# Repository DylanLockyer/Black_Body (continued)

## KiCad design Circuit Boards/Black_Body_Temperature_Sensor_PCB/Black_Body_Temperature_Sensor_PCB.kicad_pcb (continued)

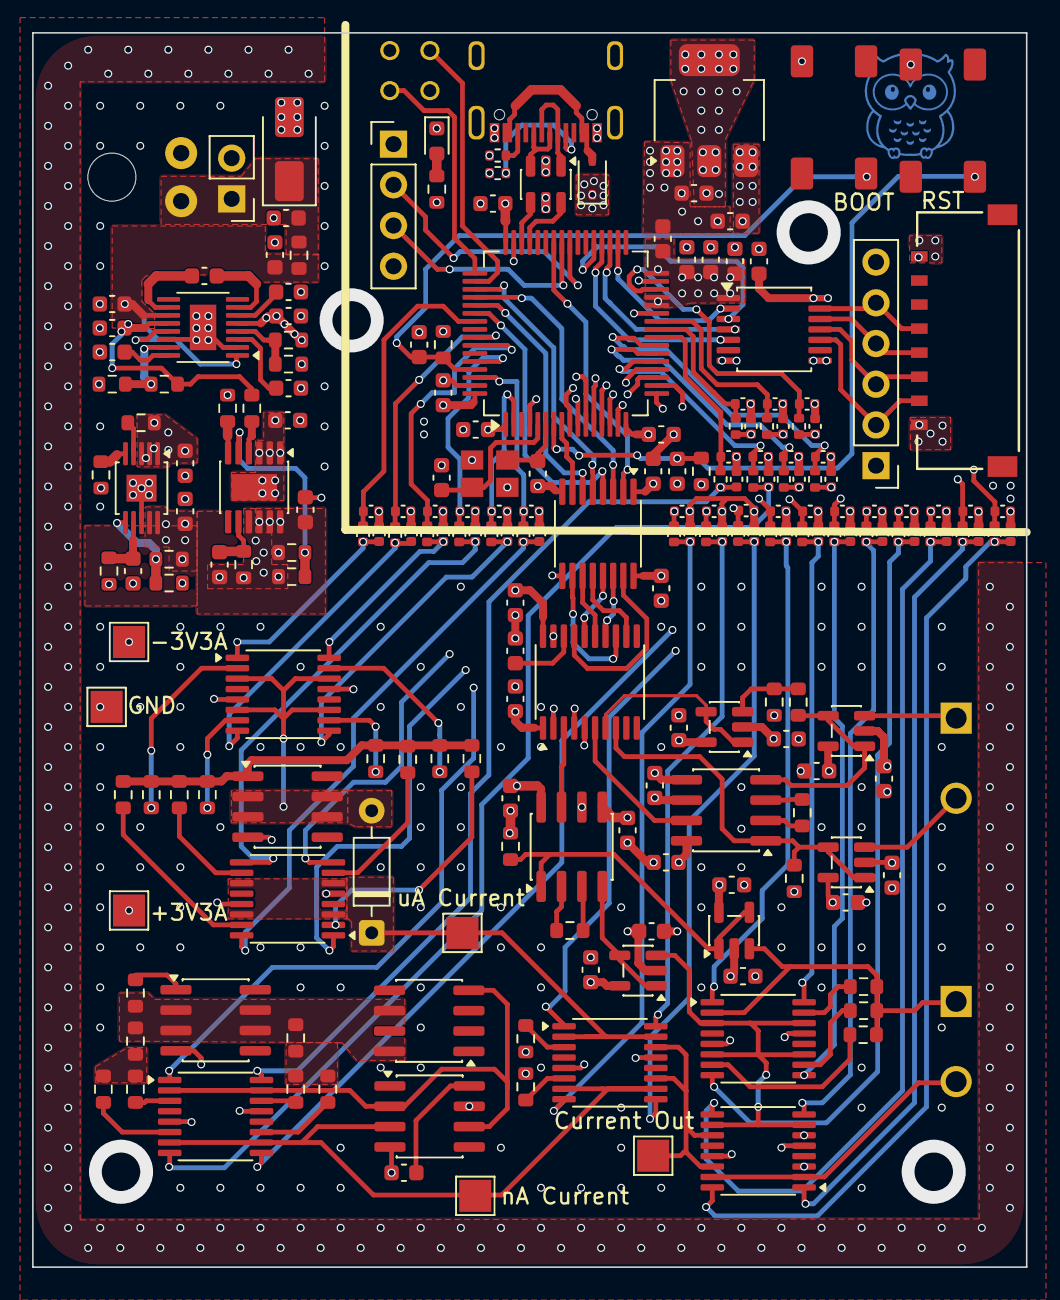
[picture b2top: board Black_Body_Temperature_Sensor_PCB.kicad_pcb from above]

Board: 6 copper layers, 62.0 x 77.0 mm, 216 parts (0 on the bottom side), 155 nets.

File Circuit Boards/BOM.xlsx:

Designator | Footprint | Quantity | Value | LCSC Part #
C201, C202, C203, C204, C205, C206, C207, C208, C209, C210, C211, C212, C213, C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 | 0402 | 48 | 2u2 | GRM155R61E225ME15D
C309 | 0603 | 1 | 200pf | CL10C201JB8NNNC
C501 | 0603 | 1 | 220nf | GCM188R71H224KA64D
C502, C503, C504, C505, C506, C507, C508, C509, C510, C511, C512, C513, C514, C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 | 0603 | 29 | 0.1uf | CL10B104KB8NNNC
C601, C602, C606, C607, C609, C614, C615, C712 | 0603 | 8 | 10uf | GRM188R6YA106MA73D
C603 | 0603 | 1 | 1uf | C0603C105K4RACTU
C604, C605 | 0603 | 2 | 10nf | CL10B103KB8NNNC
C608, C610, C611, C612, C613 | 0603 | 5 | 4.7uf | CL10A475KO8NNNC
C703, C705 | 0603 | 2 | 28pf | CL10C270JB8NNNC
C715 | 0603 | 1 | 22uf | CL10A226MP8NUNE
D201 | D_DO-35_SOD27_P7.62mm_Horizontal | 1 | 1N457 | 1N457
D301 | SOIC-8_3.9x4.9mm_P1.27mm | 1 | LT1004-1.2 | LT1004CS8-1.2#TRPBF
D601 | D_SMA | 1 | SMAJ24A | SMAJ24A
D701 | D_SOD-323 | 1 | 1N5819WS | 1N5819WS
J401, J402 | CUI_TB002-500-02BE | 2 | Screw_Terminal_01x02 | TB002-500-02BE
J702 | CONN_5040500891_MOL | 1 | 5040500891 | 5040500891
J703 | UJ20-C-H-G-SMT-1-P16-TR | 1 | USB_C_Receptacle_USB2.0_16P | UJ20-C-H-G-SMT-1-P16-TR
P601 | 436500200 2-pin | 1 | 436500200 | 436500200
Q201, Q202, Q301, Q401, Q402, Q403 | TSSOP-16_4.4x5mm_P0.65mm | 6 | TMUX1112PWR | TMUX1112PWR
R201, R202, R203, R204, R205, R206, R207, R208, R301, R302, R303, R304, R401, R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 | 0402 | 26 | 5.1k | RT0402BRD075K1L
R209 | 0603 | 1 | 133 | RQ73C1J133RBTD
R210, R211 | 0603 | 2 | 1.33k | ERA-3AEB1331V
R212, R213 | 0603 | 2 | 13.3k | ERA-3AEB1332V
R214, R215 | 0603 | 2 | 134k | ERA-3AEB1333V
R216 | 0603 | 1 | 1.33M | RK73H1JTTD1334F
R305, R502, R504 | 0603 | 3 | 10M | CRCW060310M0DHEAP
R306 | 0603 | 1 | 22.6k | ERA-3AEB2262V
R307 | 0603 | 1 | 100k | ERA-3AEB104V
R308 | 0603 | 1 | 100M | HVC0603T1006FET
R309 | 0603 | 1 | 226k | ERA-3AEB2263V
R310 | 0603 | 1 | 1M | RN73H1JTTD1004B25
R311 | 0603 | 1 | 2.7k | ERA-3AEB272V
R405 | 0603 | 1 | 4.99 | RN73C1J4R99BTD
R406, R606, R616 | 0603 | 3 | 500 | ERA-3AEB4990V
R407, R605, R608 | 0603 | 3 | 33.2k | ERA-3AEB3322V
R412, R413, R505, R506, R703, R704 | 0603 | 6 | 10k | ERA-3AEB103V
R501, R503 | 0603 | 2 | 50 | ERA-3AEB49R9V
R601, R604 | 0603 | 2 | 569k | RN73H1JTTD5693B50
R602, R603, R607, R609 | 0603 | 4 | 180k | ERA-3AEB184V
R610 | 0603 | 1 | 7.5k | ERA-3AEB752V
R611, R613 | 0603 | 2 | 448k | RT0603BRD07448KL
R612, R614 | 0603 | 2 | 50k | RT0603BRD0750KL
SW701, SW702 | 430471035826 | 2 | SW_MEC_5E | 430471035826
U201, U301 | SOIC-8_3.9x4.9mm_P1.27mm | 2 | LM334M | LM334M
U302 | SOIC-8_3.9x4.9mm_P1.27mm | 1 | LT1008 | LT1008S8#PBF
U501, U502, U503, U504, U509 | SOT-23-5 | 5 | OPA376xxDBV | OPA376AIDBVR
U505, U506 | SOIC-8_3.9x4.9mm_P1.27mm | 2 | AD8421ARZ | AD8421ARZ
U507 | TSSOP-20_4.4x6.5mm_P0.65mm | 1 | ADS131M04xPW | ADS131M04IPWR
U508 | SSOP-16_3.9x4.9mm_P0.635mm | 1 | ISO7762FDBQ | ISO7762FDBQ
U601 | MSOP-16-1EP_3x4.039mm_P0.5mm_EP1.651x2.845mm | 1 | LTC3260xMSE | LTC3260EMSE#TRPBF
U602 | MSOP-12-1EP_3x4.039mm_P0.65mm_EP1.651x2.845mm | 1 | LT3094xMSE | LT3094EMSE#TRPBF
U603 | MSOP-10-1EP_3x3mm_P0.5mm_EP1.68x1.88mm | 1 | LT3042xMSE | LT3042EMSE#TRPBF
U701 | TSSOP-14_4.4x5mm_P0.65mm | 1 | TXU0304 | TXU0304
U702 | ABM8G-25.000MHZ-18-D2Y-T | 1 | ABM8G-25.000MHZ-18-D2Y-T | ABM8G-25.000MHZ-18-D2Y-T
U703 | SOT-23-6 | 1 | USBLC6-2SC6 | USBLC6-2SC6c
U704 | LQFP-64_10x10mm_P0.5mm | 1 | STM32G431RBTx | STM32G431RBT6
U705 | SOT-223-3_TabPin2 | 1 | AMS1117-3.3 | AMS1117-3.3
Heater |  | 4 | TBH25P10R0JE | TBH25P10R0JE
Mating pwr |  | 3
Mating signal |  | 1
C201, C307, C308, C309 | 0603 | 4 | 10uf | GRM188R6YA106MA73D
C202, C204, C207, C301, C305, C306, C310, C311, C312 | 0603 | 9 | 100nf | CL10B104KB8NNNC
C203, C206 | 0603 | 2 | 22uf | CL10A226MP8NUNE
C205, C302, C303, C304 | 0603 | 4 | 1uf | C0603C105K4RACTU
D201 | 0603 | 1 | RED | LTST-C191KRKT
D202 | D_SOD-323 | 1 | 1N5819WS | 1N5819WS
J201 | CONN_5040500891_MOL | 1 | 5040500891 | 5040500891
J203 | UJ20-C-H-G-SMT-1-P16-TR | 1 | USB_C_Receptacle_USB2.0_16P | UJ20-C-H-G-SMT-1-P16-TR
L301 | SRR1208 | 1 | SRR1208-120ML | SRR1208-120ML
P301, P302 | 436500200 2-pin | 2 | 436500200 | 436500200
Q302 | TO-126-3_Vertical | 1 | BD139 | BD139
R201, R203, R204, R205, R308 | 0603 | 5 | 10k | ERA-3AEB103V
R202, R302 | 0603 | 2 | 1.33k | ERA-3AEB1331V
R206, R207, R303, R311 | 0402 | 4 | 5.1k | RT0402BRD075K1L
R301 | 0805 | 1 | 100m | RCWE0805R100FKEA
R304, R305 | 0603 | 2 | 500 | ERA-3AEB4990V
R306 | 2512 | 1 | 5.0999999999999996 | CRM2512-FX-5R10ELF
R307 | 0603 | 1 | 100k | ERA-3AEB104V
R309 | 0603 | 1 | 162k | CRCW0603162KFKEA
R310 | 0603 | 1 | 22.6k | ERA-3AEB2262V
SW201, SW202 | 430471035826 | 2 | SW_MEC_5E | 430471035826
U201 | SOT-223-3_TabPin2 | 1 | AMS1117-3.3 | AMS1117-3.3
U202 | ESP32-S3-WROOM-1 | 1 | ESP32-S3-WROOM-1-N8R8 | ESP32-S3-WROOM-1-N8R8
U203 | SOT-23-6 | 1 | USBLC6-2SC6 | USBLC6-2SC6
U301 | TSSOP-10_3x3mm_P0.5mm | 1 | DAC60501ZDGSR | DAC60501ZDGSR
U302 | SOT-23-6 | 1 | INA181A2IDBVR | INA181A2IDBVR
U303 | SOT-23-5 | 1 | TLV9061xDBV | LM358BAIDR
U304 | SOT-23-6 | 1 | LMR51420XFDDCR | LMR51420XFDDCR

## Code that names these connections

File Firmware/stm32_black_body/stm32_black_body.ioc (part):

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Mcu.Name=STM32G431R(6-8-B)Tx
Mcu.Package=LQFP64
Mcu.UserName=STM32G431RBTx
PA0.GPIOParameters=GPIO_Label
PA0.GPIO_Label=i_sense_sel2
PA0.Signal=GPIO_Output
PA1.GPIOParameters=GPIO_Label
PA1.GPIO_Label=i_sense_sel3
PA1.Signal=GPIO_Output
PA11.Mode=Device
PA11.Signal=USB_DM
PA12.Mode=Device
PA12.Signal=USB_DP
PA13.Mode=Serial_Wire
PA13.Signal=SYS_JTMS-SWDIO
PA14.Mode=Serial_Wire
PA14.Signal=SYS_JTCK-SWCLK
PA15.GPIOParameters=GPIO_Label
PA15.GPIO_Label=SPI3_CS
PA15.Signal=GPIO_Output
PA2.GPIOParameters=GPIO_Label
PA2.GPIO_Label=hbridge_sel4
PA2.Signal=GPIO_Output
PA3.GPIOParameters=GPIO_Label
PA3.GPIO_Label=i_sense_sel4
PA3.Signal=GPIO_Output
PA4.GPIOParameters=GPIO_Label
PA4.GPIO_Label=hbridge_sel3
PA4.Signal=GPIO_Output
PA5.GPIOParameters=GPIO_Label
PA5.GPIO_Label=hbridge_sel1
PA5.Signal=GPIO_Output
PA6.GPIOParameters=GPIO_Label
PA6.GPIO_Label=hbridge_sel2
PA6.Signal=GPIO_Output
PA7.GPIOParameters=GPIO_Label
PA7.GPIO_Label=sel_10na_pos
PA7.Signal=GPIO_Output
PA8.Signal=S_TIM1_CH1
PB0.GPIOParameters=GPIO_Label
PB0.GPIO_Label=sel_100na_neg
PB0.Signal=GPIO_Output
PB1.GPIOParameters=GPIO_Label
PB1.GPIO_Label=sel_t_1ma
PB1.Signal=GPIO_Output
PB10.GPIOParameters=GPIO_Label
PB10.GPIO_Label=sel_10na_neg
PB10.Signal=GPIO_Output
PB12.GPIOParameters=GPIO_Label
PB12.GPIO_Label=SPI2_CS
PB12.Signal=GPIO_Output
PB13.Mode=Full_Duplex_Master
PB13.Signal=SPI2_SCK
PB14.Mode=Full_Duplex_Master
PB14.Signal=SPI2_MISO
PB15.Mode=Full_Duplex_Master
PB15.Signal=SPI2_MOSI
PB2.GPIOParameters=GPIO_Label
PB2.GPIO_Label=sel_t_1ua
PB2.Signal=GPIO_Output
PB4.GPIOParameters=GPIO_Label
PB4.GPIO_Label=sel_v_100ua
PB4.Signal=GPIO_Output
PB5.GPIOParameters=GPIO_Label
PB5.GPIO_Label=sel_v_1ua
PB5.Signal=GPIO_Output
PB7.GPIOParameters=GPIO_Label
PB7.GPIO_Label=sel_t_100ua
PB7.Signal=GPIO_Output
PB9.GPIOParameters=GPIO_Label
PB9.GPIO_Label=sel_t_10ua
PB9.Signal=GPIO_Output
PC0.GPIOParameters=GPIO_Label,GPIO_ModeDefaultEXTI
PC0.GPIO_Label=ADC_DRDY
PC0.GPIO_ModeDefaultEXTI=GPIO_MODE_IT_FALLING
PC0.Signal=GPXTI0
PC1.GPIOParameters=GPIO_Label
PC1.GPIO_Label=i_source_sel3
PC1.Signal=GPIO_Output
PC10.Mode=Full_Duplex_Master
PC10.Signal=SPI3_SCK
PC11.Mode=Full_Duplex_Master
PC11.Signal=SPI3_MISO
PC12.Mode=Full_Duplex_Master
PC12.Signal=SPI3_MOSI
PC13.GPIOParameters=GPIO_Label
PC13.GPIO_Label=sel_v_1ma
PC13.Signal=GPIO_Output
PC15-OSC32_OUT.GPIOParameters=GPIO_Label
PC15-OSC32_OUT.GPIO_Label=i_source_sel4
PC15-OSC32_OUT.Signal=GPIO_Output
PC2.GPIOParameters=GPIO_Label
PC2.GPIO_Label=i_source_sel2
PC2.Signal=GPIO_Output
PC3.GPIOParameters=GPIO_Label
PC3.GPIO_Label=i_sense_sel1
PC3.Signal=GPIO_Output
PC4.GPIOParameters=GPIO_Label
PC4.GPIO_Label=sel_100na_pos
PC4.Signal=GPIO_Output
PC5.GPIOParameters=GPIO_Label
PC5.GPIO_Label=i_source_sel1
PC5.Signal=GPIO_Output
PC8.Mode=I2C
PC8.Signal=I2C3_SCL
PC9.Mode=I2C
PC9.Signal=I2C3_SDA
PD2.GPIOParameters=GPIO_Label
PD2.GPIO_Label=sel_v_10ua
PD2.Signal=GPIO_Output
PF0-OSC_IN.Mode=HSE-External-Oscillator
PF0-OSC_IN.Signal=RCC_OSC_IN
PF1-OSC_OUT.Mode=HSE-External-Oscillator
PF1-OSC_OUT.Signal=RCC_OSC_OUT
RCC.HSE_VALUE=25000000
RCC.SYSCLKFreq_VALUE=170000000
RCC.SYSCLKSource=RCC_SYSCLKSOURCE_PLLCLK
board=custom

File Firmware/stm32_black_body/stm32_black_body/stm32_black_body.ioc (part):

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Mcu.Name=STM32G431R(6-8-B)Tx
Mcu.Package=LQFP64
Mcu.UserName=STM32G431RBTx
PA0.Signal=GPIO_Output
PA1.Signal=GPIO_Output
PA11.Mode=Device
PA11.Signal=USB_DM
PA12.Mode=Device
PA12.Signal=USB_DP
PA13.Mode=Serial_Wire
PA13.Signal=SYS_JTMS-SWDIO
PA14.Mode=Serial_Wire
PA14.Signal=SYS_JTCK-SWCLK
PA15.Mode=NSS_Signal_Hard_Input
PA15.Signal=SPI3_NSS
PA2.Signal=GPIO_Output
PA3.Signal=GPIO_Output
PA4.Signal=GPIO_Output
PA5.Signal=GPIO_Output
PA6.Signal=GPIO_Output
PA7.Signal=GPIO_Output
PA8.GPIOParameters=GPIO_Label
PA8.GPIO_Label=ADC_CLKIN
PA8.Mode=Clock-out
PA8.Signal=RCC_MCO
PB0.Signal=GPIO_Output
PB1.Signal=GPIO_Output
PB10.Signal=GPIO_Output
PB12.Mode=NSS_Signal_Hard_Output
PB12.Signal=SPI2_NSS
PB13.Mode=Full_Duplex_Master
PB13.Signal=SPI2_SCK
PB14.Mode=Full_Duplex_Master
PB14.Signal=SPI2_MISO
PB15.Mode=Full_Duplex_Master
PB15.Signal=SPI2_MOSI
PB2.Signal=GPIO_Output
PB4.Signal=GPIO_Output
PB5.Signal=GPIO_Output
PB7.Signal=GPIO_Output
PB9.Signal=GPIO_Output
PC0.GPIOParameters=GPIO_Label
PC0.GPIO_Label=ADC_DRDY
PC0.Signal=GPIO_Input
PC1.Signal=GPIO_Output
PC10.Mode=Full_Duplex_Slave
PC10.Signal=SPI3_SCK
PC11.Mode=Full_Duplex_Slave
PC11.Signal=SPI3_MISO
PC12.Mode=Full_Duplex_Slave
PC12.Signal=SPI3_MOSI
PC13.Signal=GPIO_Output
PC15-OSC32_OUT.Signal=GPIO_Output
PC2.Signal=GPIO_Output
PC3.Signal=GPIO_Output
PC4.Signal=GPIO_Output
PC5.Signal=GPIO_Output
PC8.Mode=I2C
PC8.Signal=I2C3_SCL
PC9.Mode=I2C
PC9.Signal=I2C3_SDA
PD2.Signal=GPIO_Output
PF0-OSC_IN.Mode=HSE-External-Oscillator
PF0-OSC_IN.Signal=RCC_OSC_IN
PF1-OSC_OUT.Mode=HSE-External-Oscillator
PF1-OSC_OUT.Signal=RCC_OSC_OUT
RCC.HSE_VALUE=25000000
RCC.SYSCLKFreq_VALUE=170000000
RCC.SYSCLKSource=RCC_SYSCLKSOURCE_PLLCLK
board=custom

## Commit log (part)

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2026-05-11 Simulation
2026-05-12 Finished base schematic, missing thermal sensor
2026-05-13 Documentation and file organization
2026-05-13 Buck spice file not working, created new pcb
2026-05-20 Current source simulations
2026-05-26 current source simulation, pcb 2->1 switches
2026-05-26 temp sensor pcb progress
2026-05-28 power simulation
2026-06-02 Schematic ready for review
2026-06-03 Temperature Sensor Schematic Done, awaiting review
2026-06-05 Heater PCB done (to review)
2026-06-05 Updating ESP32 pcb documentation
2026-06-05 Updating silkscreen
2026-06-05 Updating photo
2026-06-05 Updating documentation
2026-06-08 Temp sensor schematic done
2026-06-10 temp pcb analog layout done
2026-06-10 Digital section done
2026-06-12 Complete except for recommended changes
2026-06-15 Heater switched from pwm to vccs
2026-06-16 heater ready to order
2026-06-18 Temp probe bom done
2026-06-20 Designs finished - order placed
2026-06-23 Documentation and reorganization
2026-06-23 Add MIT License to the project
